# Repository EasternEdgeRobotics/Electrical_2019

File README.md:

# 2019-Electrical
Electrical files for MATE 2019

Looking for documentation? [See the wiki.](https://github.com/EasternEdgeRobotics/2019/wiki)

Looking for control software? [See the 2019 repo.](https://github.com/EasternEdgeRobotics/2019)

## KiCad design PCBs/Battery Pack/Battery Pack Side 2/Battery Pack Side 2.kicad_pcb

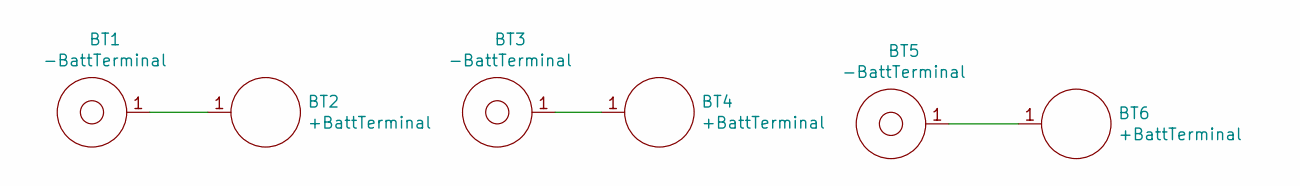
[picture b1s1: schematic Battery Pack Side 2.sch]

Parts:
BT1, BT3, BT5: -BattTerminal; -Batt Terminal; Digikey 36-240-ND
BT2, BT4, BT6: +BattTerminal; +Batt Terminal; Digikey SN-T5-2-ND

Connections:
unnamed: BT1.1, BT2.1
unnamed: BT3.1, BT4.1
unnamed: BT5.1, BT6.1

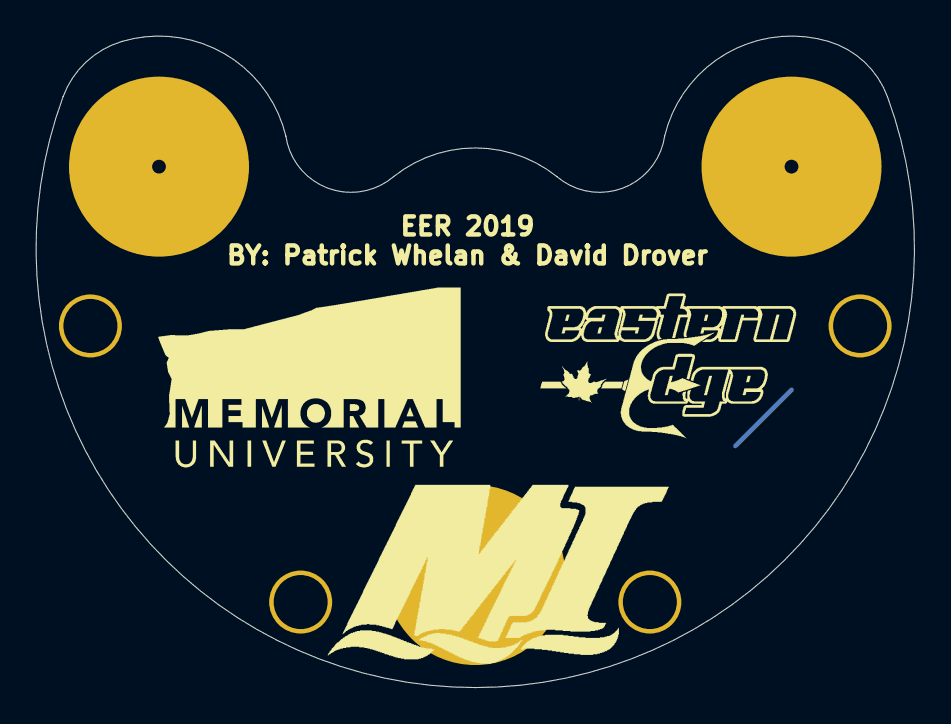
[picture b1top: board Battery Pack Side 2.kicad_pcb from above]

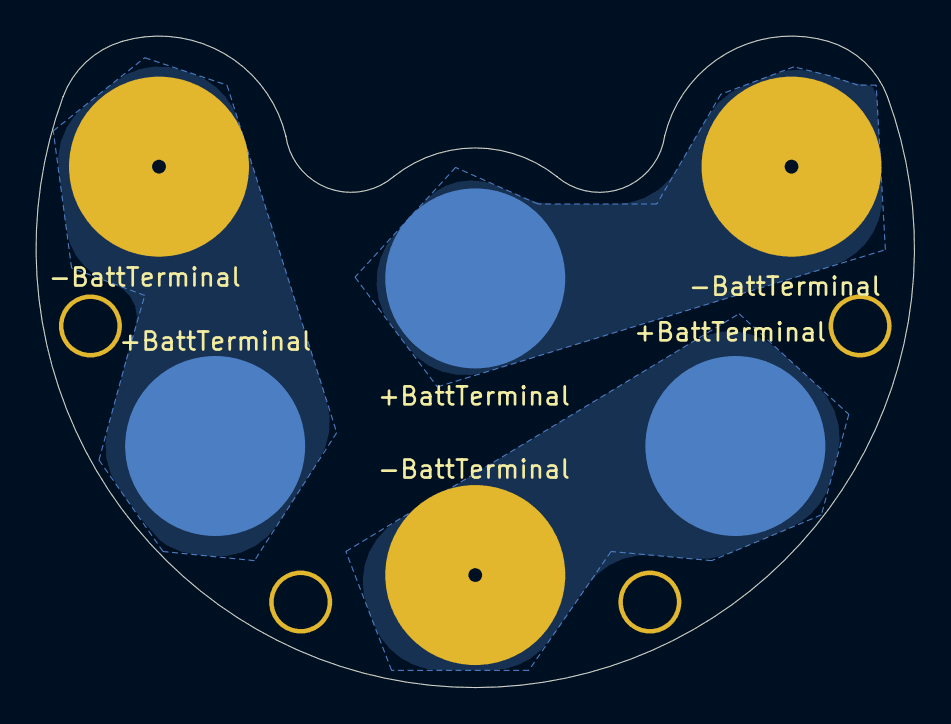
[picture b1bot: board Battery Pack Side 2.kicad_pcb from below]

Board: 2 copper layers, 48.8 x 36.2 mm, 9 parts (6 on the bottom side), 3 nets.

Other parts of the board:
U$12: EERLOGO
U$15: MUNLOGO
U$16: MILOGO

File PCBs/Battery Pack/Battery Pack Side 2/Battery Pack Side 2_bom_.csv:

Component,Description,Part,References,Value,Footprint,Quantity Per PCB,Datasheet,Digikey
1,,+BattTerminal,BT2 BT4 BT6,+BattTerminal,+Batt Terminal,3,http://www.memoryprotectiondevices.com/datasheets/SN-T5-2-da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,SN-T5-2-ND
2,,-BattTerminal,BT1 BT3 BT5,-BattTerminal,-Batt Terminal,3,,36-240-ND





Component Groups:,2
Component Count:,6
Fitted Components:,6
Number of PCBs:,1
Total components:,6
Schematic Version:,
Schematic Date:,
BoM Date:,2019-01-30 8:44:34 PM
Schematic Source:,C:\Users\pwhel\Documents\KiCAD Projects\Battery Pack\Battery Pack Side 2\Battery Pack Side 2.sch
KiCad Version:,Eeschema (5.0.1)-3

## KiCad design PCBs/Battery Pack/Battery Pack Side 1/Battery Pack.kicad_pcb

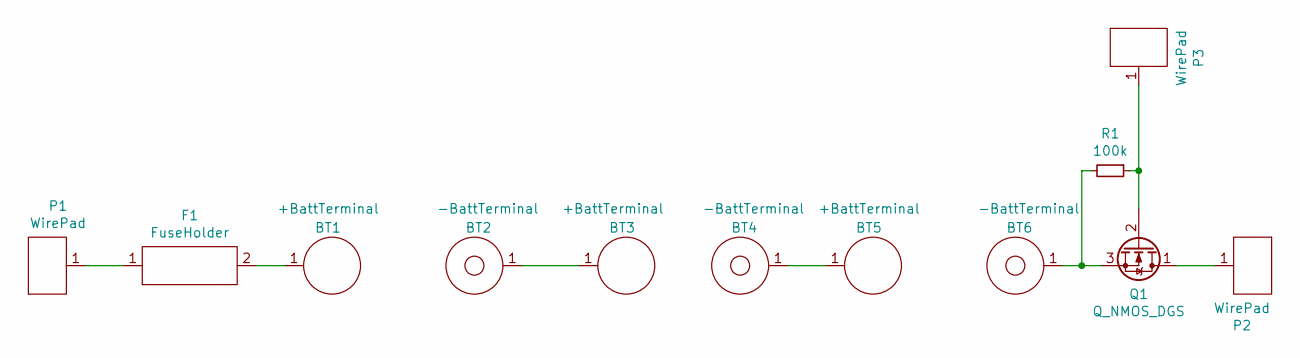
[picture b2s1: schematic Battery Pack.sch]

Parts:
BT1, BT3, BT5: +BattTerminal; +Batt Terminal
BT2, BT4, BT6: -BattTerminal; -Batt Terminal
F1: FuseHolder; Glass Fuse Holder
P1, P2: WirePad; Wire Pad
P3: WirePad; Small Wire Pad
Q1: Q_NMOS_DGS; TRANS_DMN2020UFCL-7
R1: 100k; R_0805

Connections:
unnamed: BT1.1, F1.2
unnamed: BT2.1, BT3.1
unnamed: BT4.1, BT5.1
unnamed: BT6.1, Q1.3 (S), R1.2
unnamed: F1.1, P1.1
unnamed: P2.1, Q1.1 (D)
unnamed: P3.1, Q1.2 (G), R1.1

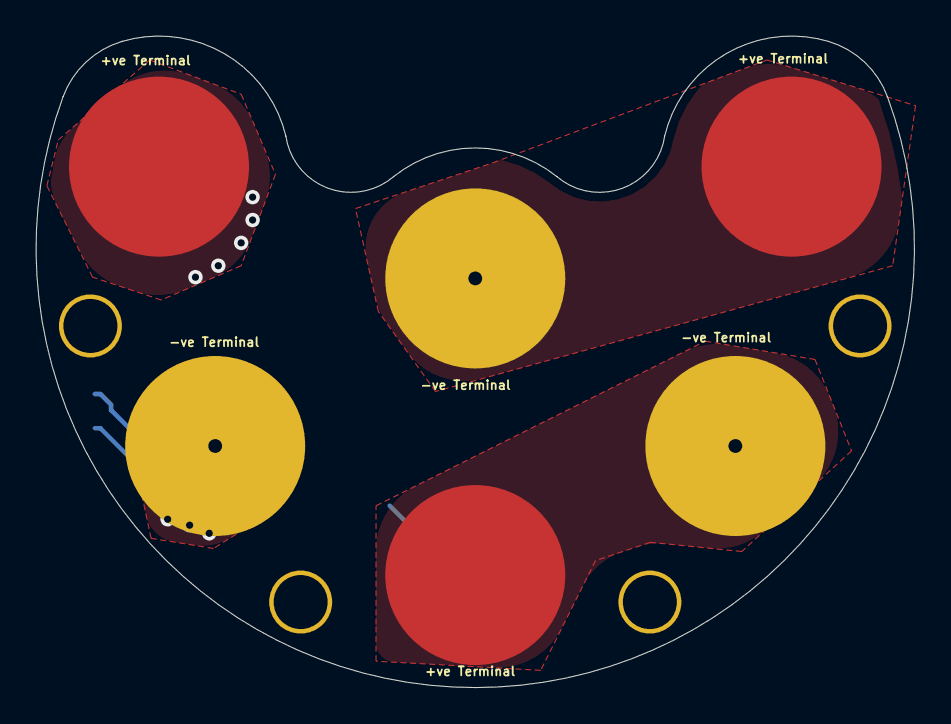
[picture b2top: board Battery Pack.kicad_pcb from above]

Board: 2 copper layers, 48.8 x 36.2 mm, 12 parts (1 on the bottom side), 7 nets.

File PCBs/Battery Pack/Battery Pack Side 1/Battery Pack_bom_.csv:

Component,Description,Part,References,Value,Footprint,Quantity Per PCB,Datasheet,Digikey
1,,+BattTerminal,BT1 BT3 BT5,+BattTerminal,+Batt Terminal,3,http://www.memoryprotectiondevices.com/datasheets/SN-T5-2-da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,SN-T5-2-ND
2,,-BattTerminal,BT2 BT4 BT6,-BattTerminal,-Batt Terminal,3,,36-240-ND
3,,FuseHolder,F1,FuseHolder,Glass Fuse Holder,1,https://www.littelfuse.com/data/en/data_sheets/littelfuse_fu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,F4236-ND
4,,WirePad,P1 P2,WirePad,Wire Pad,2,,
5,,WirePad,P3,WirePad,Small Wire Pad,1,,
6,"N-MOSFET transistor, drain/gate/source",Q_NMOS_DGS,Q1,Q_NMOS_DGS,TRANS_DMN2020UFCL-7,1,https://www.diodes.com/assets/Datasheets/DMN2020UFCL.pdf,DMN2020UFCL-7DICT-ND
7,"Resistor, small symbol",R_Small,R1,100k,R_0805,1,https://www.rohm.com/datasheet/ESR01MZPF/esr-e,RHM100KKCT-ND





Component Groups:,7
Component Count:,12
Fitted Components:,12
Number of PCBs:,1
Total components:,12
Schematic Version:,
Schematic Date:,
BoM Date:,2019-01-30 8:37:53 PM
Schematic Source:,C:\Users\pwhel\Documents\KiCAD Projects\Battery Pack\Battery Pack Side 1\Battery Pack.sch
KiCad Version:,Eeschema (5.0.1)-3

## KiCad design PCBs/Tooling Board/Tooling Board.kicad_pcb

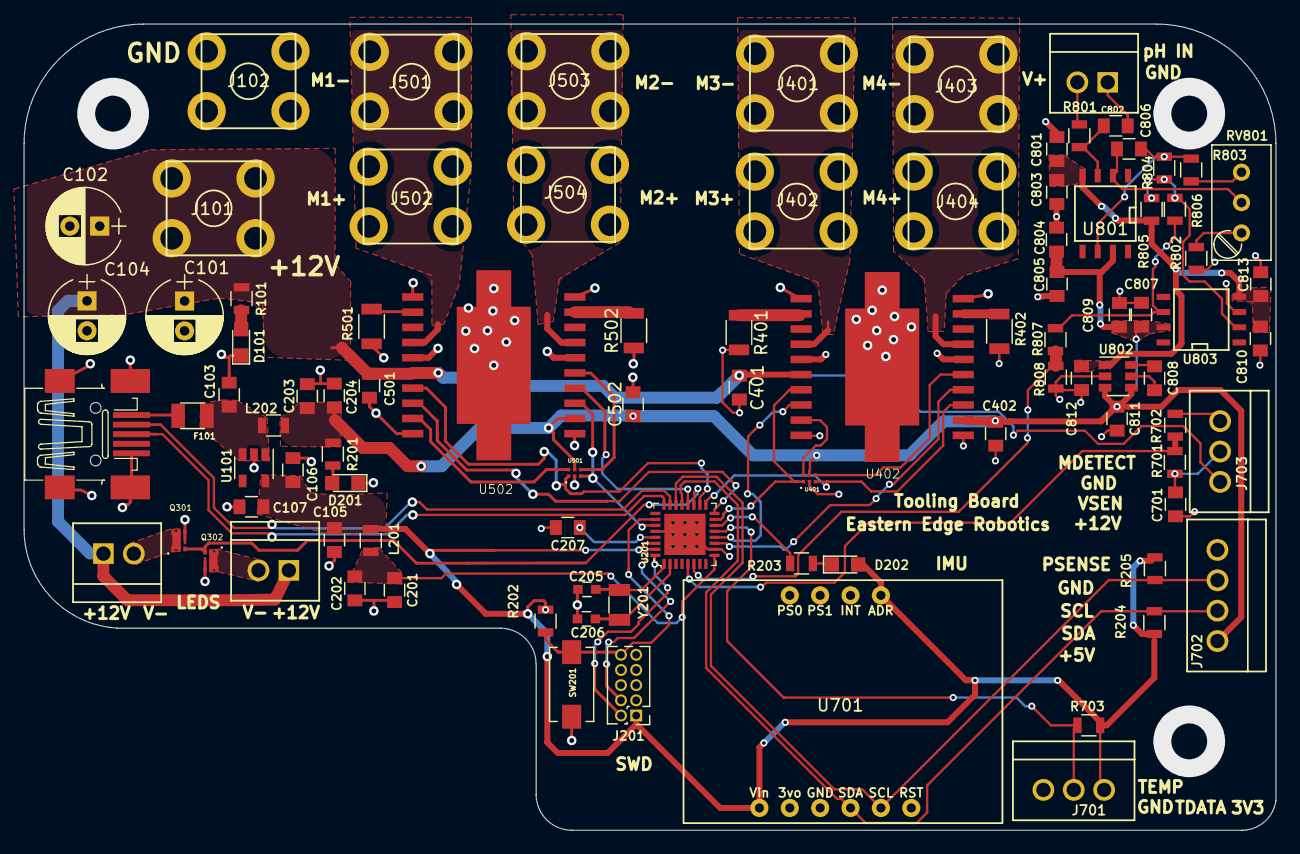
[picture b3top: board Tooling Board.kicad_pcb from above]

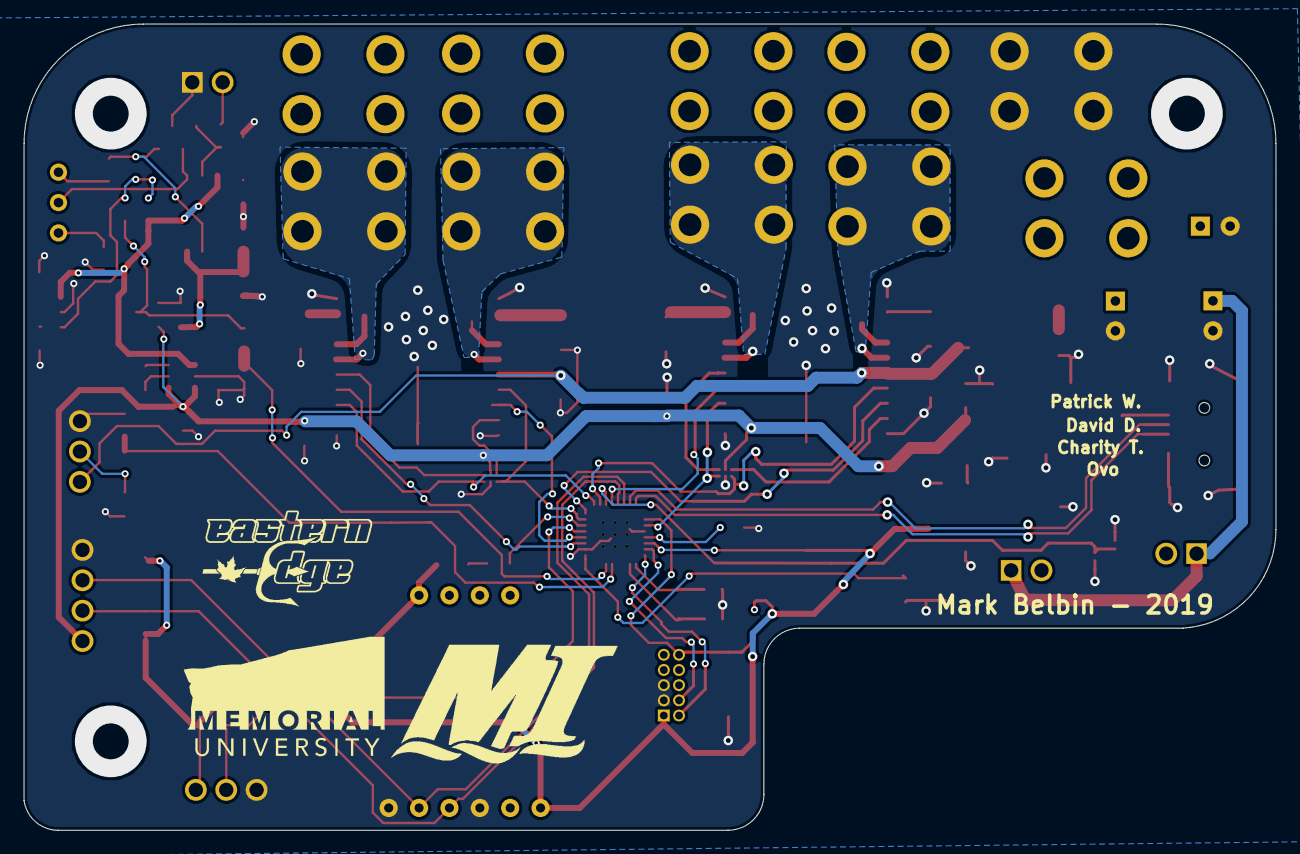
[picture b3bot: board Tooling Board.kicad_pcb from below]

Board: 2 copper layers, 104.7 x 67.4 mm, 95 parts (3 on the bottom side), 63 nets.

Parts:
C101, C102, C104: 220uF; CP_Radial_D6.3mm_P2.50mm
C103, C106, C204, C701, C806: 1uF; C_0805
C105, C201, C203, C801, C805, C807, C810: 10uF; C_0805
C107, C202, C207: 0.1uF; C_0805
C205, C206: 22pF; C_0603
C401, C402, C501, C502, C803, C804, C809, C813: 100nF; C_0805
C802: 2.2nF; C_0805
C808, C811, C812: 2.2uF; C_0805
D101: BLUE; LED_0805
D201: RED; LED_0805
D202: ORNGE; LED_0805
F101: 500mA; Fuse_SMD1206_Reflow
J101, J102, J401, J402, J403, J404, J501, J502, J503, J504: Screw Terminal; RingTerminal
J103: USB_B_Mini; 32005-201
J201: Conn_02x05_Odd_Even; Pin_Header_Straight_2x05_Pitch1.27mm
J301, J302, J801: Conn_01x02; 1x2_molex_llc_new
J701, J703: Conn_01x03; 1x3_molex_llc
J702: Conn_01x04; 1x4_molex_llc
L201, L202: Ferrite_Bead; L_0805
Q301: Q1; TRANS_DMN2020UFCL-7
Q302: Q_NMOS_DGS; TRANS_DMN2020UFCL-7
R101, R802: 1k; R_0805
R201: 330; R_0805
R202, R204, R205: 10k; R_0805
R203: 680; R_0805
R401, R402, R501, R502: 0.5; R_1206
R701, R805: 75k; R_0805
R702: 25k; R_0805
R703: 4.7k; R_0805
R801: 4.7M; R_0805
R803: 2.2k; R_0805
R804, R806: 30k; R_0805
R807: 20k; R_0805
R808: 33k; R_0805
RV801: 5k; Potentiometer_Trimmer_Bourns_3296W
SW201: SW_Push; SW_SPST_EVQPE1
U101: TLV733P; SOT-23-5
U201: ATSAMD21E18A-MFTCT-ND; QFN-32-1EP_5x5mm
U401, U501: 74LVC2G14; PSON50P140X100X40-6N
U402, U502: LN298P; POWER-SO20
U701: ADA_IMU; IMU
U801: CA3140AM; SOIC-8-N
U802: LM2776; SOT-23-6
U803: TL081BCDG4; SOIC-8-N
U$12: EERLOGO
U$15: MUNLOGO
U$16: MILOGO
Y201: 32.7680kHz; Crystal_SMD_3215-2pin_3.2x1.5mm

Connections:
3V3_FILT: C201.1, C202.1, L201.1, U201.9
+3V3: C105.1, C106.1, C107.1, D202.2, J201.1, J701.1, L201.2, R202.1, R204.1, R205.1, R703.1, U101.5, U201.30, U701.1, U701.10
+5V: C203.1, C204.1, C402.1, C502.1, C804.2, C805.2, C807.1, C809.1, C811.1, J702.1, L202.1, R201.1, U401.5, U402.12, U501.5, U502.12, U801.7, U802.3, U802.4, U803.7
+12V: C101.1, C102.1, C104.1, C401.1, C501.1, J101.1, J301.1, J302.1, J703.1, R101.1, U402.6, U502.6
-5V: C801.1, C803.1, C810.1, C812.1, C813.1, R805.2, U801.4, U802.1, U803.4
/Actuators/DCMotor1-2/Input2: U401.6, U402.9
/Actuators/DCMotor1-2/Input4: U401.4, U402.15
/Actuators/DCMotor3-4/Input2: U501.6, U502.9
/Actuators/DCMotor3-4/Input4: U501.4, U502.15
/MicroController/+5V_IN: C103.1, F101.1, L202.2, U101.1, U101.3
DirA1: U201.15, U401.1, U402.7
DirA2: U201.18, U501.1, U502.7
DirB1: U201.17, U401.3, U402.13
DirB2: U201.27, U501.3, U502.13
EnableA1: U201.12, U402.8
EnableA2: U201.16, U502.8
EnableB1: U201.11, U402.14
EnableB2: U201.20, U502.14
GND: C101.2, C102.2, C103.2, C104.2, C105.2, C106.2, C107.2, C201.2, C202.2, C203.2, C204.2, C205.2, C206.2, C207.2, C401.2, C402.2, C501.2, C502.2, C701.2, C801.2, C802.2, C803.2, C804.1, C805.1, C807.2, C809.2, C810.2, C811.2, C812.2, C813.2, D101.1, D201.1, J102.1, J103.5, J103.6, J201.3, J201.5, J701.3, J702.4, J703.3, J801.1, Q301.3, Q302.3, R401.2, R402.1, R501.2, R502.1, R702.1, R802.2, R808.2, SW201.1, U101.2, U201.10, U201.28, U201.33, U401.2, U402.1, U402.10, U402.11, U402.20, U501.2, U502.1, U502.10, U502.11, U502.20, U701.3, U701.6, U802.2, U803.3
LED: Q301.2, Q302.2, U201.19
unnamed: C205.1, U201.1, Y201.1
unnamed: C206.1, U201.2, Y201.2
unnamed: C207.1, U201.29
unnamed: C701.1, J703.2, R701.2
unnamed: C802.1, R801.1, U801.3
unnamed: C806.1, R803.1, R804.2, U801.6
unnamed: C806.2, RV801.2, U801.2
unnamed: C808.1, U802.5
unnamed: C808.2, U802.6
unnamed: D101.2, R101.2
unnamed: D201.2, R201.2
unnamed: D202.1, R203.2
unnamed: F101.2, J103.1
unnamed: J301.2, Q301.1
unnamed: J302.2, Q302.1
unnamed: J401.1, U402.4
unnamed: J402.1, U402.5
unnamed: J403.1, U402.17
unnamed: J404.1, U402.16
unnamed: J501.1, U502.4
unnamed: J502.1, U502.5
unnamed: J503.1, U502.17
unnamed: J504.1, U502.16
unnamed: J801.2, R801.2
unnamed: R203.1, U201.14
unnamed: R401.1, U402.2
unnamed: R402.2, U402.19
unnamed: R501.1, U502.2
unnamed: R502.2, U502.19
unnamed: R802.1, RV801.1
unnamed: R803.2, RV801.3
unnamed: R804.1, R805.1, R806.2, U803.2
unnamed: R806.1, R807.1, U803.6
SCL: J702.3, R205.2, U201.22, U701.5
SDA: J702.2, R204.2, U201.21, U701.4
SWCLK: J201.4, U201.31
SWDIO: J201.2, U201.32
T_DATA: J701.2, R703.2, U201.13
USB+: J103.3, U201.24
USB-: J103.2, U201.23
V_METAL: R701.1, R702.2, U201.5
V_PH: R807.2, R808.1, U201.6
~RESET~: J201.10, R202.2, SW201.2, U201.26

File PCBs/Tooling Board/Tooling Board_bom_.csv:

Component,Description,Part,References,Value,Footprint,Quantity Per PCB,Datasheet,Digikey,Status
1,Unpolarized capacitor,C,C107 C202 C207 C401 C402 C501 C502 C803 C804 C809 C813,0.1uF,C_0805,11,http://www.yageo.com/documents/recent/UPY-GPHC_X7R_6.3V-to-5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,311-1140-1-ND,
2,Unpolarized capacitor,C,C105 C201 C203 C801 C805 C807 C810,10uF,C_0805,7,http://www.samsungsem.com/kr/support/product-search/mlcc/__i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,1276-2872-1-ND,
3,Unpolarized capacitor,C,C103 C106 C204 C701 C806,1uF,C_0805,5,http://www.samsungsem.com/kr/support/product-search/mlcc/__i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,1276-6470-1-ND,
4,Unpolarized capacitor,C,C802,2.2nF,C_0805,1,~,587-1293-1-ND,
5,Unpolarized capacitor,C,C808 C811 C812,2.2uF,C_0805,3,~,587-1293-1-ND,
6,Unpolarized capacitor,C,C101 C102 C104,220uF,CP_Radial_D6.3mm_P2.50mm,3,https://content.kemet.com/datasheets/KEM_A4067_A750.pdf,399-13664-ND,
7,Unpolarized capacitor,C,C205 C206,22pF,C_0603,2,311-3925-1-ND,,
8,Light emitting diode,LED,D101,BLUE,LED_0805,1,https://katalog.we-online.de/led/datasheet/150080BS75000.pdf,732-4982-1-ND,
9,Light emitting diode,LED,D202,ORNGE,LED_0805,1,160-1413-1-ND,,
10,Light emitting diode,LED,D201,RED,LED_0805,1,732-4984-1-ND,,
11,Fuse,Fuse,F101,500mA,Fuse_SMD1206_Reflow,1,https://belfuse.com/resources/datasheets/circuitprotection/d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,507-1075-1-ND,
12,"Generic connector, single row, 01x02, script generated (kicad-library-utils/schlib/autogen/connector/)",Conn_01x02,J301 J302 J801,Conn_01x02,1x2_molex_llc_new,3,~,WM4800-ND,
13,"Generic connector, single row, 01x03, script generated (kicad-library-utils/schlib/autogen/connector/)",Conn_01x03,J701 J703,Conn_01x03,1x3_molex_llc,2,~,WM4801-ND,
14,"Generic connector, single row, 01x04, script generated (kicad-library-utils/schlib/autogen/connector/)",Conn_01x04,J702,Conn_01x04,1x4_molex_llc,1,~,WM4802-ND,
15,"Generic connector, double row, 02x05, odd/even pin numbering scheme (row 1 odd numbers, row 2 even numbers), script generated (kicad-library-utils/schlib/autogen/connector/)",Conn_02x05_Odd_Even,J201,Conn_02x05_Odd_Even,Pin_Header_Straight_2x05_Pitch1.27mm,1,609-3712-ND,,
16,"Generic screw terminal, single row, 01x01, script generated (kicad-library-utils/schlib/autogen/connector/)",Screw_Terminal_01x01,J101 J102 J401 J402 J403 J404 J501 J502 J503 J504,Screw Terminal,RingTerminal,10,~,36-7770-ND,
17,USB Mini Type B connector,USB_B_Mini,J103,USB_B_Mini,32005-201,1,~,151-1206-1-ND,
18,Ferrite bead,Ferrite_Bead,L201 L202,Ferrite_Bead,L_0805,2,490-9706-1-ND,,
19,"N-MOSFET transistor, drain/gate/source",Q_NMOS_DGS,Q301 Q302,Q_NMOS_DGS,TRANS_DMN2020UFCL-7,2,https://www.digikey.ca/product-detail/en/diodes-incorporated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,,
20,"Resistor, US symbol",R_US,R401 R402 R501 R502,0.5,R_1206,4,~,CSR1206FKR500CT-ND,
21,"Resistor, US symbol",R_US,R202 R204 R205,10k,R_0805,3,RNCP0805FTD10K0CT-ND,,
22,"Resistor, US symbol",R_US,R101,1k,R_0805,1,http://www.yageo.com/documents/recent/PYu-RT_1-to-0.01_RoHS_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,YAG1820CT-ND,
23,Resistor,R,R802,1k,R_0805,1,~,RR12P1.0KDCT-ND,
24,Resistor,R,R803,2.2k,R_0805,1,~,311-2.20KCRCT-ND,
25,Resistor,R,R807,20k,R_0805,1,~,A126349CT-ND,
26,"Resistor, US symbol",R_US,R702,25k,R_0805,1,~,A121556CT-ND,
27,Resistor,R,R804 R806,30k,R_0805,2,~,A126360CT-ND,
28,"Resistor, US symbol",R_US,R201,330,R_0805,1,RHM330DCT-ND,,
29,Resistor,R,R808,33k,R_0805,1,~,RR12P33.0KDCT-ND,
30,Resistor,R,R801,4.7M,R_0805,1,~,RMCF0805FT4M70CT-ND,
31,"Resistor, US symbol",R_US,R703,4.7k,R_0805,1,~,311-4.70KCRCT-ND,
32,"Resistor, US symbol",R_US,R203,680,R_0805,1,RHM680DCT-ND,,
33,"Resistor, US symbol",R_US,R701,75k,R_0805,1,~,YAG3750CT-ND,
34,Resistor,R,R805,75k,R_0805,1,~,YAG3750CT-ND,
35,"Potentiometer, US symbol",R_POT_US,RV801,5k,Potentiometer_Trimmer_Bourns_3296W,1,https://www.digikey.ca/product-detail/en/bourns-inc/3296W-1-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,490-2888-ND,
36,"Push button switch, generic, two pins",SW_Push,SW201,SW_Push,SW_SPST_EVQPE1,1,401-1707-1-ND,,
37,,74LVC2G14-EER,U401 U501,74LVC2G14,PSON50P140X100X40-6N,2,https://www.digikey.ca/product-detail/en/diodes-incorporated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,,
38,,ADA_IMU-EER,U701,ADA_IMU,IMU,1,,,
39,IC MCU 32BIT 64KB FLASH 48QFN,ATSAMD21E18A-MFT,U201,ATSAMD21E18A-MFTCT-ND,QFN-32-1EP_5x5mm,1,ATSAMD21E18A-MFTCT-ND,,Active
40,"4.5MHz, BiMOS Operational Amplifier with MOSFET Input/Bipolar Output, DIP-8/SOIC-8",CA3140,U801,CA3140AM,SOIC-8-N,1,https://www.digikey.ca/product-detail/en/renesas-electronics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,CA3140AMZ-ND,
41,"Switched capacitor inverter, inverts positive voltage +2.7 to +5.5V to negative, 200 mA, SOT-23-6",LM2776,U802,LM2776,SOT-23-6,1,https://www.digikey.ca/product-detail/en/texas-instruments/L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,296-43957-1-ND,
42,,LN298P-EER,U402 U502,LN298P,POWER-SO20,2,https://www.digikey.ca/product-detail/en/stmicroelectronics/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,,
43,"4.5MHz, BiMOS Operational Amplifier with MOSFET Input/Bipolar Output, DIP-8/SOIC-8",CA3140,U803,TL081BCDG4,SOIC-8-N,1,https://www.digikey.ca/products/en?keywords=TL081BCDG4,296-34259-5-ND,
44,"200 mA Low Dropout Voltage Regulator, Fixed Output 1.8V, SOT-23-5",TLV70018_SOT23-5,U101,TLV733P,SOT-23-5,1,http://www.ti.com/lit/ds/symlink/tlv700.pdf,296-40673-1-ND,
45,Two pin crystal,Crystal,Y201,32.7680kHz,Crystal_SMD_3215-2pin_3.2x1.5mm,1,887-2605-1-ND,,
,,,,,,,,,
,,,,,,,,,
,,,,,,,,,
,,,,,,,,,
,,,,,,,,,
Component Groups:,45,,,,,,,,
Component Count:,92,,,,,,,,
Fitted Components:,92,,,,,,,,
Number of PCBs:,1,,,,,,,,
Total components:,92,,,,,,,,
Schematic Version:,,,,,,,,,
Schematic Date:,,,,,,,,,
BoM Date:,13/02/2019 19:33,,,,,,,,
Schematic Source:,C:\Users\David\Documents\eastern_edge_git\2019-Electrical\PCBs\Tooling Board\Tooling Board.sch,,,,,,,,
KiCad Version:,Eeschema (5.0.1)-3,,,,,,,,

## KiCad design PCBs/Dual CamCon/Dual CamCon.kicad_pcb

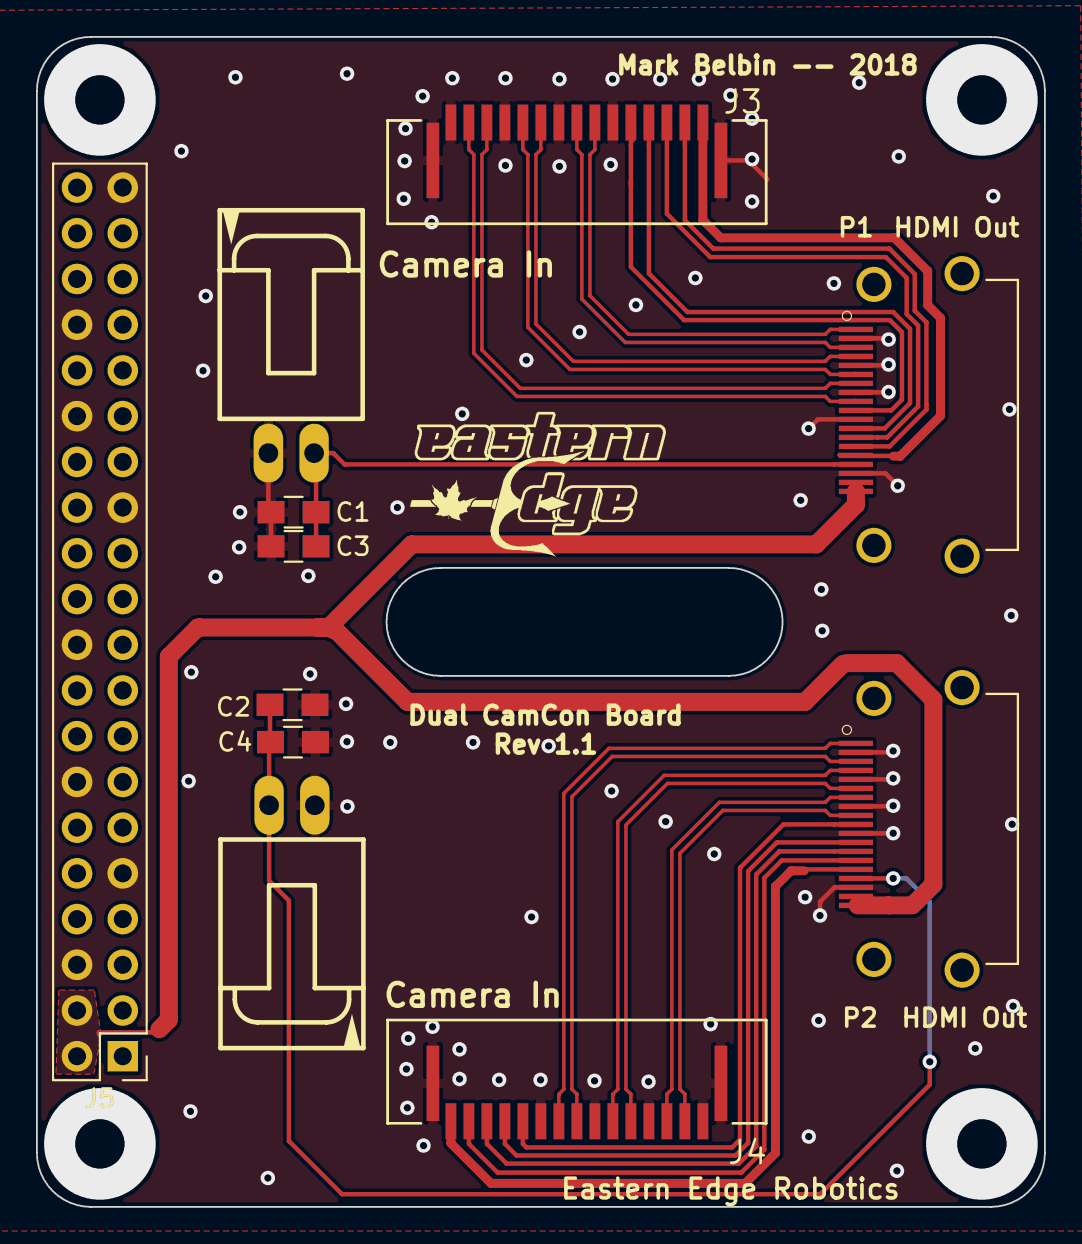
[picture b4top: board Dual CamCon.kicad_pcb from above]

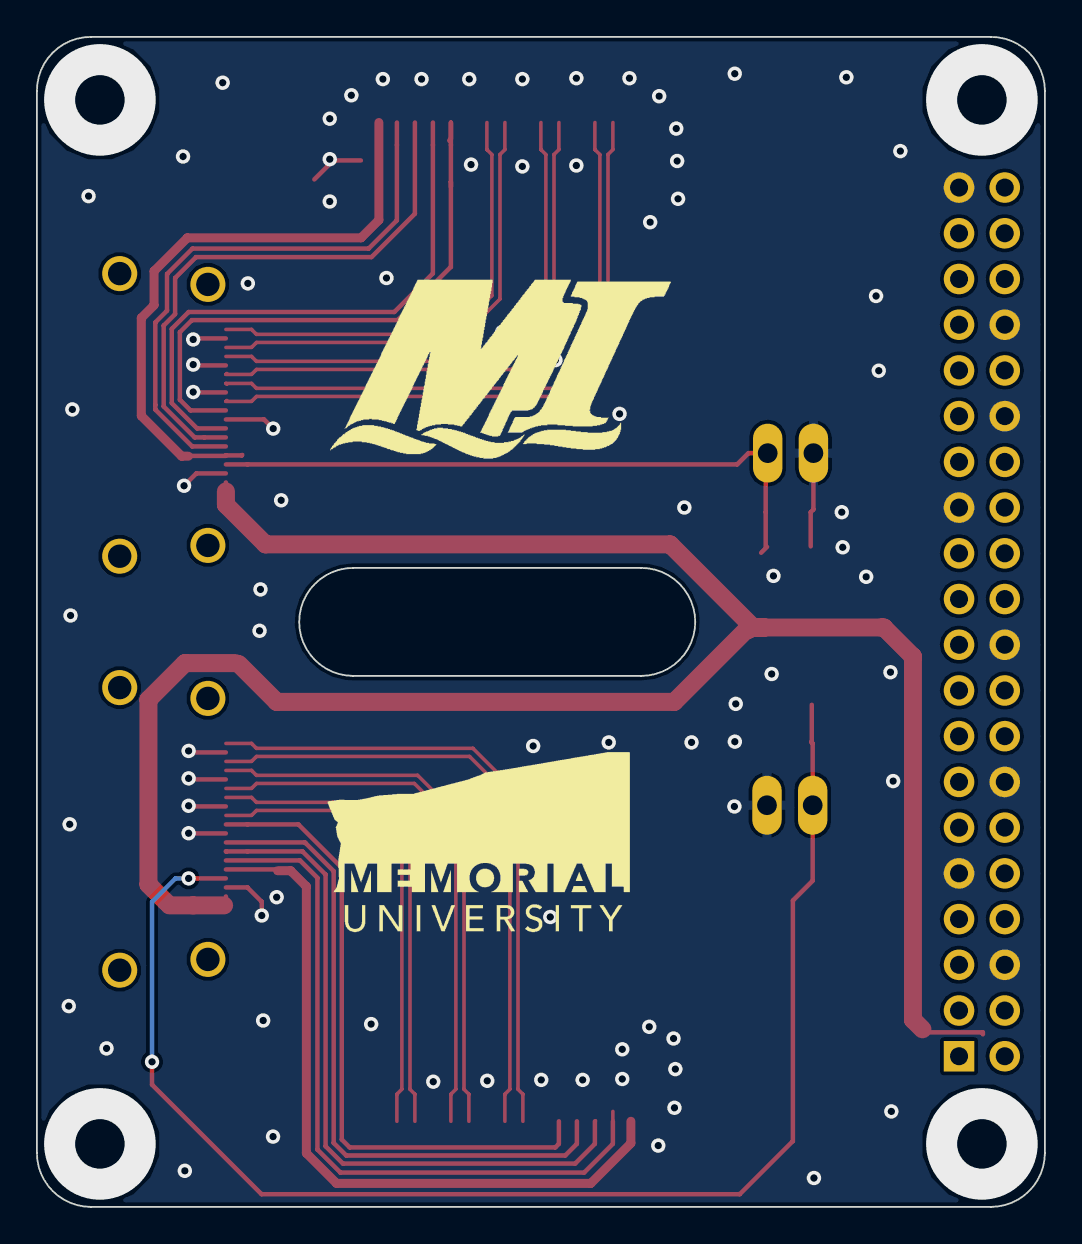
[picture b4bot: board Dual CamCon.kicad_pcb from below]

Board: 2 copper layers, 56.0 x 65.0 mm, 13 parts (2 on the bottom side), 26 nets.

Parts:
C1, C2, C3, C4: C; C_0805_HandSoldering
J1, J2: Servo Input; 70553-02
J3, J4: Camera In; CON15_1X15_DRB_SFW
J5: Raspberry Pi GPIO; RaspberryGPIO
P1, P2: HDMI Out; FCI_10029449-001RLF
U$15: MUNLOGO
U$16: MILOGO

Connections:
+5V: J5.2, J5.4, P1.18, P1.19, P2.18, P2.19
/CAM1_3V3: J3.1, P1.15
/CAM1_C+: J3.7, P1.1
/CAM1_C-: J3.8, P1.3
/CAM1_CLK: J3.4, P1.12
/CAM1_D0+: J3.13, P1.7
/CAM1_D0-: J3.14, P1.9
/CAM1_D1+: J3.10, P1.4
/CAM1_D1-: J3.11, P1.6
/CAM1_GPIO: J3.5, P1.10
/CAM1_SCL: J3.3, P1.13
/CAM1_SDA: J3.2, P1.14
/CAM2_3V3: J4.1, P2.15
/CAM2_C+: J4.7, P2.1
/CAM2_C-: J4.8, P2.3
/CAM2_CLK: J4.4, P2.12
/CAM2_D0+: J4.13, P2.7
/CAM2_D0-: J4.14, P2.9
/CAM2_D1+: J4.10, P2.4
/CAM2_D1-: J4.11, P2.6
/CAM2_GPIO: J4.5, P2.10
/CAM2_SCL: J4.3, P2.13
/CAM2_SDA: J4.2, P2.14
/Servo1: C1.1, C3.1, J1.2, P1.16
/Servo2: C2.1, C4.1, J2.2, P2.16
GND: C1.2, C2.2, C3.2, C4.2, J1.1, J2.1, J3.6, J3.9, J3.12, J3.15, J3.16, J3.17, J4.6, J4.9, J4.12, J4.15, J4.16, J4.17, J5.6, J5.9, J5.14, J5.20, J5.25, J5.30, J5.34, J5.39, P1.2, P1.5, P1.8, P1.11, P1.17, P2.2, P2.5, P2.8, P2.11, P2.17

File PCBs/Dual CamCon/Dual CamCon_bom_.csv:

Component,Description,Part,References,Value,Footprint,Quantity Per PCB,Datasheet
1,Unpolarized capacitor,C,C1 C2 C3 C4,C,C_0805_HandSoldering,4,~
2,,SFW15R-1STE1LF,J3 J4,Camera FPC Connector,CON15_1X15_DRB_SFW,2,609-1905-1-ND
3,"Generic connector, double row, 02x20, odd/even pin numbering scheme (row 1 odd numbers, row 2 even numbers), script generated (kicad-library-utils/schlib/autogen/connector/)",Conn_02x20_Odd_Even,J5,Raspberry Pi GPIO,Pin_Header_Straight_2x20_Pitch2.54mm,1,S9200-ND
4,"Generic connector, single row, 01x02, script generated (kicad-library-utils/schlib/autogen/connector/)",Conn_01x02,J1 J2,Servo Input,MOLEX_0705530001,2,WM4900-ND
5,,10029449-001RLF,P1 P2,HDMI Connector,FCI_10029449-001RLF,2,609-4614-1-ND





Component Groups:,5
Component Count:,11
Fitted Components:,11
Number of PCBs:,1
Total components:,11
Schematic Version:,
Schematic Date:,
BoM Date:,2018-10-19 10:46:09 PM
Schematic Source:,D:\ROV 2019\Github\2019\PCBs\Dual CamCon\Dual CamCon.sch
KiCad Version:,Eeschema (5.0.0)

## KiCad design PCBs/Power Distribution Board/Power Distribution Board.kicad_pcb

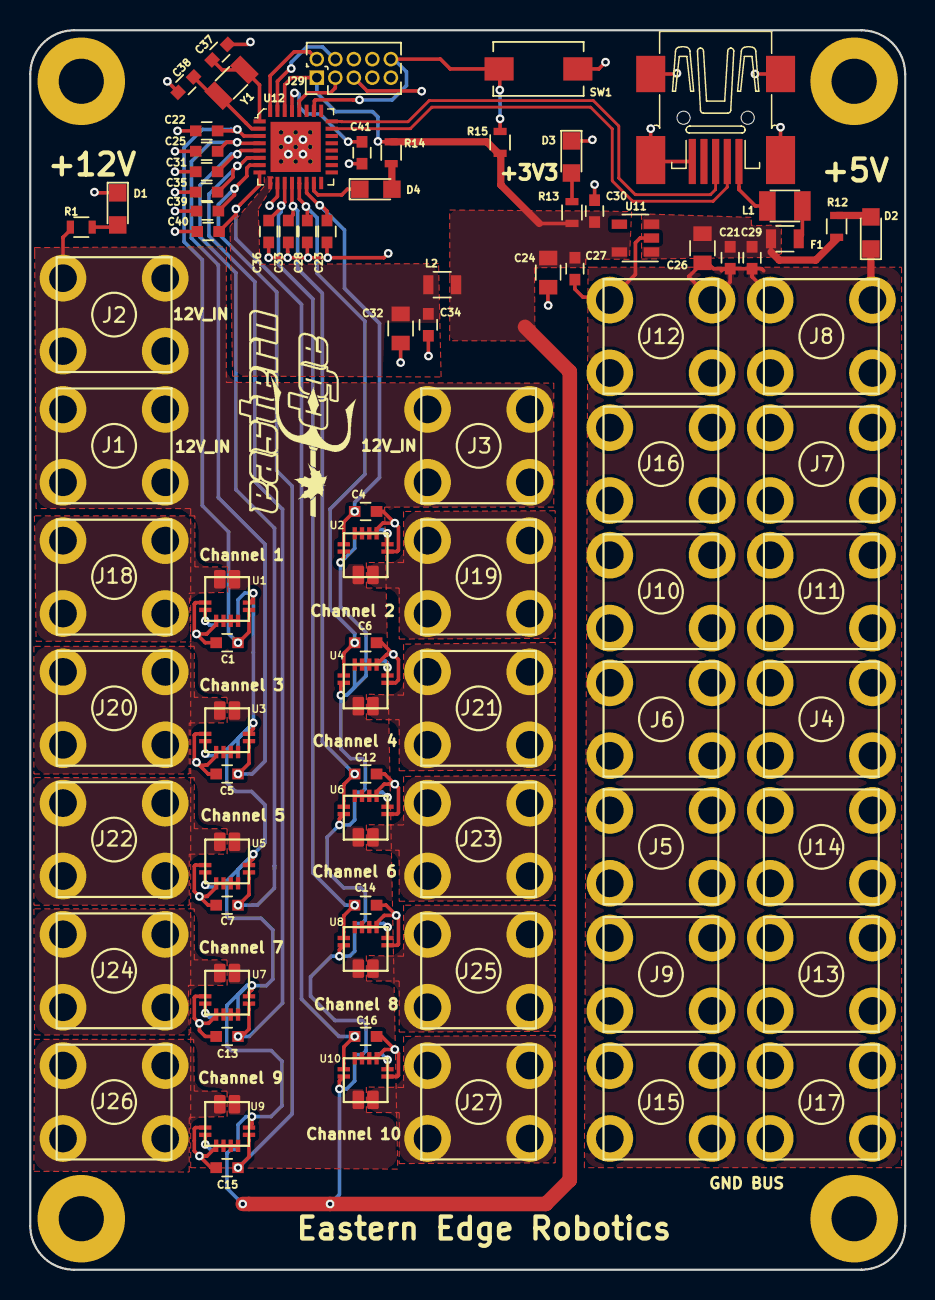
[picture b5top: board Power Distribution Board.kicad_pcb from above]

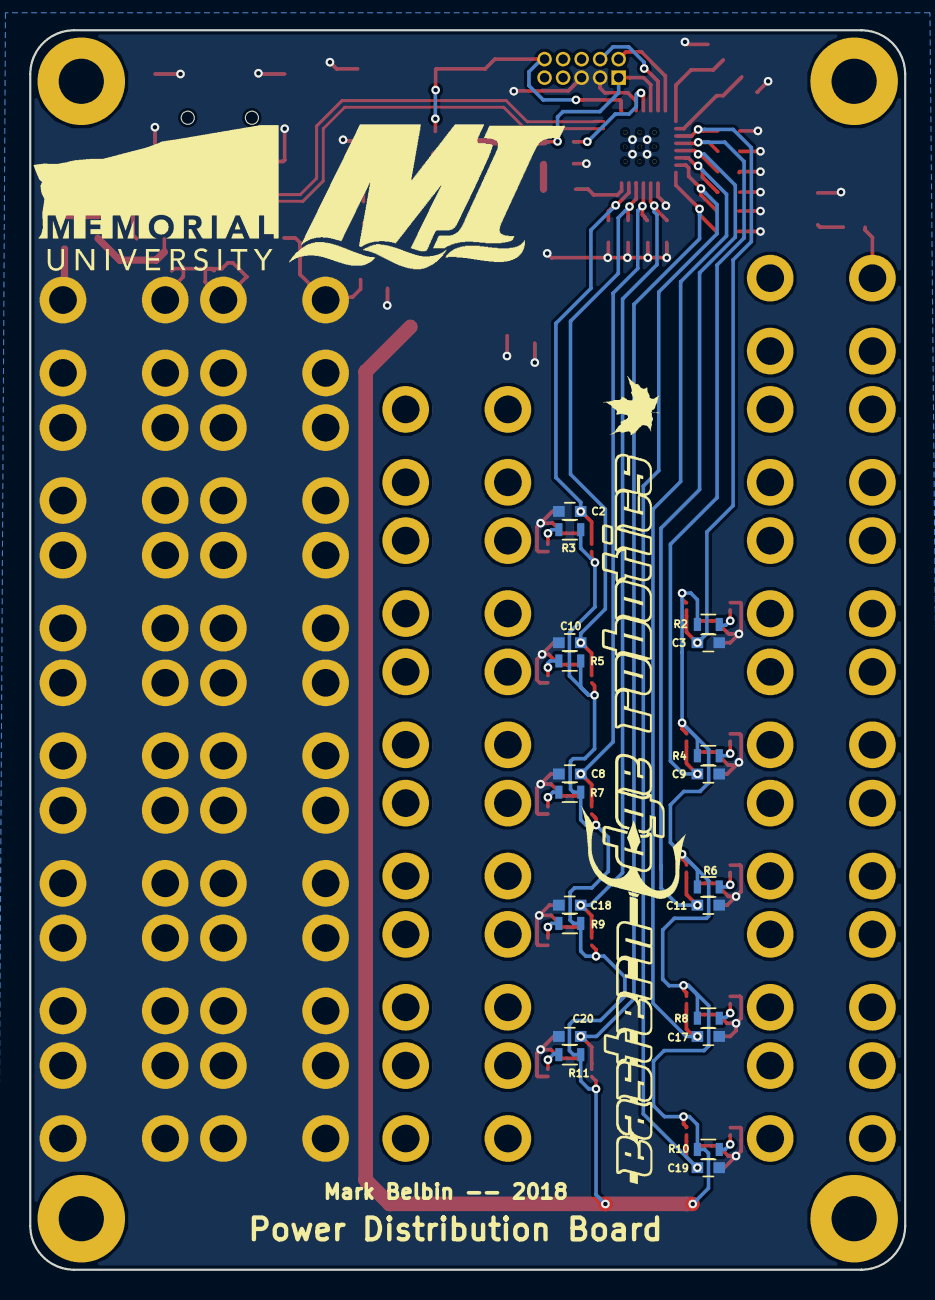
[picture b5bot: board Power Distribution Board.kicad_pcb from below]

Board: 2 copper layers, 60.0 x 85.0 mm, 110 parts (23 on the bottom side), 50 nets.

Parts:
C1, C2, C5, C6, C7, C8, C13, C14, C15, C16, C21, C22, C23, C25, C27, C28, C29, C31, C33, C35, C36, C39, C40: 1uF; C_0603
C3, C4, C9, C10, C11, C12, C17, C18, C19, C20, C30, C34, C41: 0.1uF; C_0603
C24, C26, C32: 10uF; C_0805
C37, C38: 22pF; C_0603
D1: BLUE; LED_0805
D2: RED; LED_0805
D3, D4: ORNGE; LED_0805
F1: 500mA; Fuse_SMD1206_Reflow
J1, J2, J3, J4, J5, J6, J7, J8, J9, J10, J11, J12, J13, J14, J15, J16, J17, J18, J19, J20, J21, J22, J23, J24, J25, J26, J27: Conn_01x01; RingTerminal
J28: USB_B_Mini; 32005-201
J29: Conn_02x05_Odd_Even; Pin_Header_Straight_2x05_Pitch1.27mm
L1, L2: Ferrite_Bead; L_0805
R1, R2, R3, R4, R5, R6, R7, R8, R9, R10, R11, R14: 1k; R_0603
R12: 330; R_0603
R13: 680; R_0603
R15: 10k; R_0603
SW1: SW_Push; SW_SPST_EVQPE1
U1, U2, U3, U4, U5, U6, U7, U8, U9, U10: ACS711
U11: TLV733P; SOT-23-5
U12: ATSAMD21E16L-MFT; QFN-32-1EP_5x5mm
U$12: EERLOGO
U$14: EERLOGOLONG
U$15: MUNLOGO
U$16: MILOGO
Y1: 32.7680kHz; Crystal_SMD_3215-2pin_3.2x1.5mm

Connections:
3V3_FILT: C32.1, C34.1, L2.1, U12.9
12V_IN: J1.1, J2.1, J3.1, R1.1, U1.1, U2.1, U3.1, U4.1, U5.1, U6.1, U7.1, U8.1, U9.1, U10.1
12V_OUT1: J18.1, U1.3
12V_OUT2: J19.1, U2.3
12V_OUT3: J20.1, U3.3
12V_OUT4: J21.1, U4.3
12V_OUT5: J22.1, U5.3
12V_OUT6: J23.1, U6.3
12V_OUT7: J24.1, U7.3
12V_OUT8: J25.1, U8.3
12V_OUT9: J26.1, U9.3
12V_OUT10: J27.1, U10.3
+3V3: C24.1, C27.1, C30.1, J29.1, L2.2, R2.1, R3.1, R4.1, R5.1, R6.1, R7.1, R8.1, R9.1, R10.1, R11.1, R13.1, R14.2, R15.1, U1.12, U2.12, U3.12, U4.12, U5.12, U6.12, U7.12, U8.12, U9.12, U10.12, U11.5, U12.30
+5V: C21.1, C26.1, C29.1, L1.1, R12.1, U11.1, U11.3
GND: C1.2, C2.2, C3.2, C4.2, C5.2, C6.2, C7.2, C8.2, C9.2, C10.2, C11.2, C12.2, C13.2, C14.2, C15.2, C16.2, C17.2, C18.2, C19.2, C20.2, C21.2, C22.2, C23.2, C24.2, C25.2, C26.2, C27.2, C28.2, C29.2, C30.2, C31.2, C32.2, C33.2, C34.2, C35.2, C36.2, C37.2, C38.2, C39.2, C40.2, C41.2, D1.1, D2.1, D3.1, J4.1, J5.1, J6.1, J7.1, J8.1, J9.1, J10.1, J11.1, J12.1, J13.1, J14.1, J15.1, J16.1, J17.1, J28.5, J28.6, J29.3, J29.5, SW1.1, U1.5, U1.7, U2.5, U2.7, U3.5, U3.7, U4.5, U4.7, U5.5, U5.7, U6.5, U6.7, U7.5, U7.7, U8.5, U8.7, U9.5, U9.7, U10.5, U10.7, U11.2, U12.10, U12.28, U12.33
unnamed: C37.1, U12.1, Y1.1
unnamed: C38.1, U12.2, Y1.2
unnamed: C41.1, U12.29
unnamed: D1.2, R1.2
unnamed: D2.2, R12.2
unnamed: D3.2, R13.2
unnamed: D4.1, U12.15
unnamed: D4.2, R14.1
unnamed: F1.1, L1.2
unnamed: F1.2, J28.1
unnamed: R2.2, U1.6
unnamed: R3.2, U2.6
unnamed: R4.2, U3.6
unnamed: R5.2, U4.6
unnamed: R6.2, U5.6
unnamed: R7.2, U6.6
unnamed: R8.2, U7.6
unnamed: R9.2, U8.6
unnamed: R10.2, U9.6
unnamed: R11.2, U10.6
SWCLK: J29.4, U12.31
SWDIO: J29.2, U12.32
USB+: J28.3, U12.24
USB-: J28.2, U12.23
VIOUT1: C1.1, C3.1, C22.1, U1.11, U12.3
VIOUT2: C2.1, C4.1, C23.1, U2.11, U12.14
VIOUT3: C5.1, C9.1, C25.1, U3.11, U12.4
VIOUT4: C6.1, C10.1, C28.1, U4.11, U12.13
VIOUT5: C7.1, C11.1, C31.1, U5.11, U12.5
VIOUT6: C8.1, C12.1, C33.1, U6.11, U12.12
VIOUT7: C13.1, C17.1, C35.1, U7.11, U12.6
VIOUT8: C14.1, C18.1, C36.1, U8.11, U12.11
VIOUT9: C15.1, C19.1, C39.1, U9.11, U12.7
VIOUT10: C16.1, C20.1, C40.1, U10.11, U12.8
~RESET: J29.10, R15.2, SW1.2, U12.26

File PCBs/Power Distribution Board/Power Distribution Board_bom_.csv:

Component,Description,Part,References,Value,Footprint,Quantity Per PCB,Datasheet,Status
1,Unpolarized capacitor,C,C3 C4 C9 C10 C11 C12 C17 C18 C19 C20 C30 C34 C41,0.1uF,C_0603,13,1276-1258-1-ND,
2,Unpolarized capacitor,C,C24 C26 C32,10uF,C_0805,3,1276-2399-1-ND,
3,Unpolarized capacitor,C,C1 C2 C5 C6 C7 C8 C13 C14 C15 C16 C21 C22 C23 C25 C27 C28 C29 C31 C33 C35 C36 C39 C40,1uF,C_0603,23,1276-6524-1-ND,
4,Unpolarized capacitor,C,C37 C38,22pF,C_0603,2,311-3925-1-ND,
5,LED generic,LED,D1,BLUE,LED_0805,1,732-4982-1-ND,
6,LED generic,LED,D3 D4,ORNGE,LED_0805,2,160-1413-1-ND,
7,LED generic,LED,D2,RED,LED_0805,1,732-4984-1-ND,
8,"Fuse, generic",Fuse,F1,500mA,Fuse_SMD1206_HandSoldering,1,507-1075-1-ND,
9,"Generic connector, single row, 01x01, script generated (kicad-library-utils/schlib/autogen/connector/)",Conn_01x01,J1 J2 J3 J4 J5 J6 J7 J8 J9 J10 J11 J12 J13 J14 J15 J16 J17 J18 J19 J20 J21 J22 J23 J24 J25 J26 J27,Conn_01x01,RingTerminal,27,36-7770-ND,
10,"Generic connector, double row, 02x05, odd/even pin numbering scheme (row 1 odd numbers, row 2 even numbers), script generated (kicad-library-utils/schlib/autogen/connector/)",Conn_02x05_Odd_Even,J29,Conn_02x05_Odd_Even,20021111-00010T4LF,1,609-3712-ND,
11,USB Mini Type B connector,USB_B_Mini,J28,USB_B_Mini,32005-201,1,151-1206-1-ND,
12,Ferrite bead,Ferrite_Bead,L1 L2,Ferrite_Bead,L_0805,2,490-9706-1-ND,
13,Resistor US symbol,R_US,R15,10k,R_0603,1,RNCP0603FTD10K0CT-ND,
14,Resistor US symbol,R_US,R1 R2 R3 R4 R5 R6 R7 R8 R9 R10 R11 R14,1k,R_0603,12,RNCP0603FTD1K00CT-ND,
15,Resistor US symbol,R_US,R12,330,R_0603,1,RHM330DCT-ND,
16,Resistor US symbol,R_US,R13,680,R_0603,1,RHM680DCT-ND,
17,"Push button switch, generic, two pins",SW_Push,SW1,SW_Push,SW_SPST_EVQPE1,1,401-1707-1-ND,
18,,ACS711,U1 U2 U3 U4 U5 U6 U7 U8 U9 U10,ACS711,ACS711,10,620-1482-1-ND,
19,IC MCU 32BIT 64KB FLASH 48QFN,ATSAMD21E16L-MFT,U12,ATSAMD21E16L-MFT,QFN-32-1EP_5x5mm,1,1611-ATSAMD21E16L-MFTCT-ND,Active
20,"200 mA Low Dropout Voltage Regulator, Fixed Output 1.8V, SOT-23-5",TLV70018_SOT23-5,U11,TLV733P,SOT-23-5,1,296-40673-1-ND,
21,Two pin crystal,Crystal,Y1,32.7680kHz,Crystal_SMD_3215-2pin_3.2x1.5mm,1,887-2605-1-ND,





Component Groups:,21
Component Count:,106
Fitted Components:,106
Number of PCBs:,1
Total components:,106
Schematic Version:,
Schematic Date:,
BoM Date:,2018-11-04 12:03:30 AM
Schematic Source:,D:\ROV 2019\Github\2019\PCBs\Power Distribution Board\Power Distribution Board.sch
KiCad Version:,Eeschema (5.0.0)
